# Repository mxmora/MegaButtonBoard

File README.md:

# MegaButton Board
Board for Footswitch for 2 effect and a swap the order of the effects.

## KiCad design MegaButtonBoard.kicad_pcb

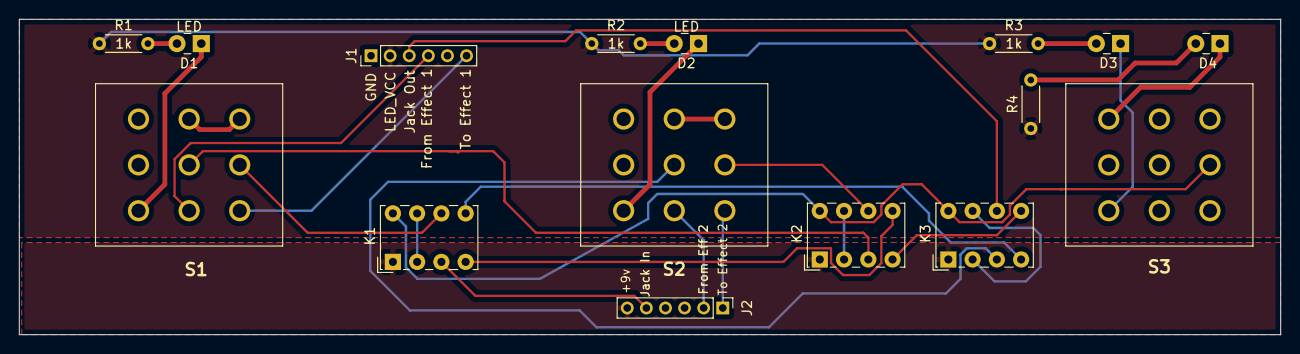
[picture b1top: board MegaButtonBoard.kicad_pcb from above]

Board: 2 copper layers, 132.1 x 33.0 mm, 16 parts (0 on the bottom side), 30 nets.

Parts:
D1, D2, D3, D4: LED; LED_Rectangular_W3.0mm_H2.0mm
J1, J2: Conn_01x06_Male; PinHeader_1x06_P2.00mm_Vertical
K1, K2, K3: G6K-2; Relay_DPDT_Omron_G6K-2P
R1, R2, R3, R4: 1k; R_Axial_DIN0204_L3.6mm_D1.6mm_P5.08mm_Horizontal
S1, S2, S3: SF17020F-0302-21R-L-015; SF17020F030221RL015

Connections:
+9V: J2.6, K1.1, K2.1, K3.1
FromEffect1: J1.4, S1.4
FromEffect2: J2.2, S2.4
GND: J1.1, S1.8, S2.8, S3.3, S3.8
InputA: K1.6, S1.2
InputB: K2.6, S2.2
Jack_Input: J2.5, K1.3
Jack_Ouput: J1.3, K3.6
LED_VCC: J1.2, R1.1, R2.1, R3.1, R4.1
unnamed: D1.1, S1.7
unnamed: D1.2, R1.2
unnamed: D2.1, S2.7
unnamed: D2.2, R2.2
unnamed: D3.1, S3.7
unnamed: D3.2, R3.2
unnamed: D4.1, S3.9
unnamed: D4.2, R4.2
unnamed: K1.2, K1.7
unnamed: K1.4, K2.5
unnamed: K1.5, K3.4
unnamed: K1.8, K2.8, K3.8, S3.2
unnamed: K2.2, K2.7
unnamed: K2.4, K3.5
unnamed: K3.2, K3.7
unnamed: S1.3, S1.6
unnamed: S2.3, S2.6
OuputA: K2.3, S1.5
OuputB: K3.3, S2.5
ToEffect1: J1.6, S1.1
ToEffect2: J2.1, S2.1

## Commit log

2019-05-20 first check in
